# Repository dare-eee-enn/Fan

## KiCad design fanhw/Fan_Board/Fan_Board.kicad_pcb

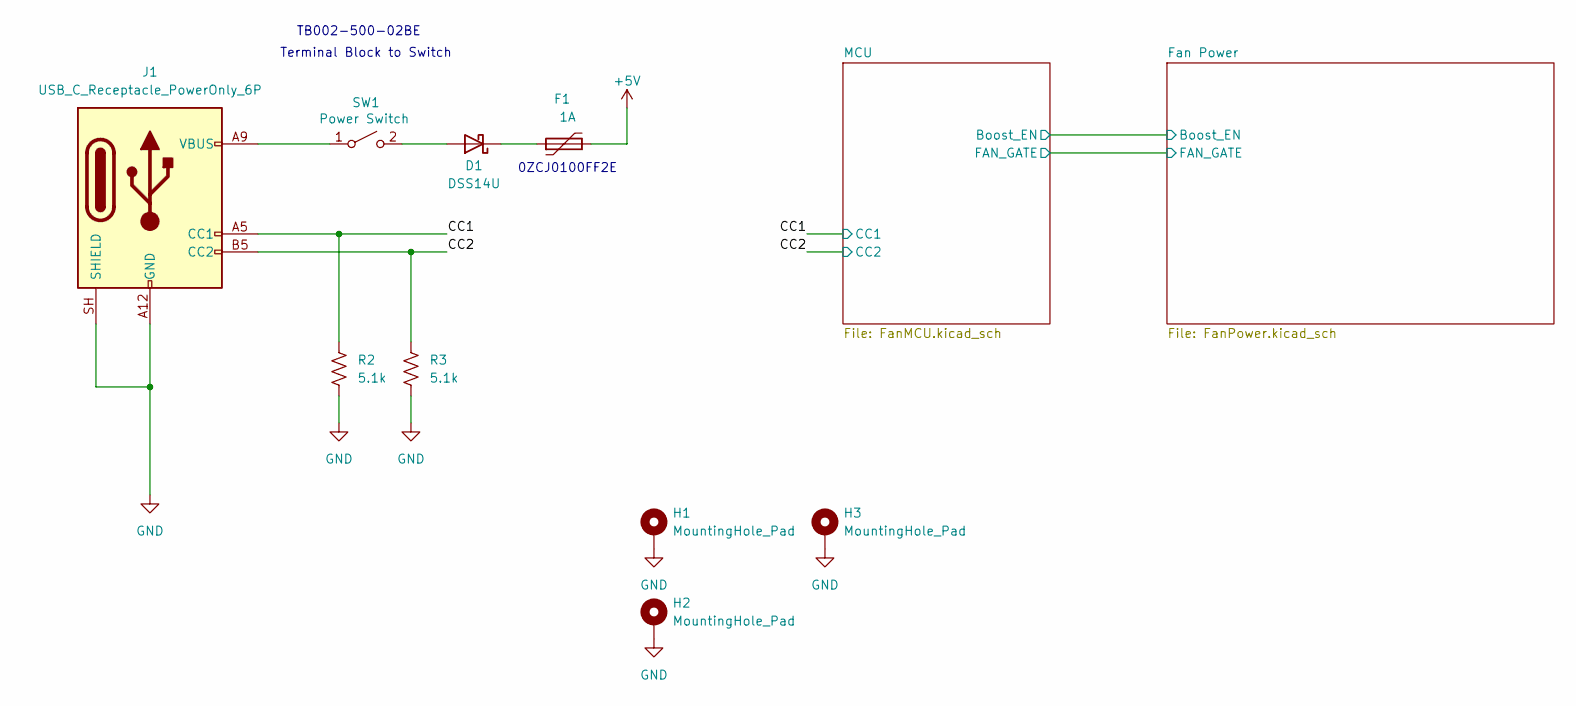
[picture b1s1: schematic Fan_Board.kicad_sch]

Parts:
D1: DSS14U; D_SOD-123F
F1: 1A; Fuse_1206_3216Metric_Pad1.42x1.75mm_HandSolder
H1, H2, H3: MountingHole_Pad; MountingHole_3.2mm_M3_DIN965_Pad
J1: USB_C_Receptacle_PowerOnly_6P; CONN_10164359-00011LF_AMP
R2, R3: 5.1k; R_0805_2012Metric_Pad1.20x1.40mm_HandSolder
SW1: Power Switch; Terminal_block

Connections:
+5V: F1.2; also elsewhere on the board
/CC1: J1.A5 (CC1), R2.1; also elsewhere on the board
/CC2: J1.B5 (CC2), R3.1; also elsewhere on the board
GND: H1.1 (1_1), H2.1 (1_1), H3.1 (1_1), J1.A12 (GND), J1.B12 (GND), J1.SH (SHIELD), R2.2, R3.2; also elsewhere on the board
unnamed: D1.2 (A), SW1.2 (B)
unnamed: D1.1 (K), F1.1
unnamed: J1.A9 (VBUS), J1.B9 (VBUS), SW1.1 (A)

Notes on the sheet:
0ZCJ0100FF2E
Terminal Block to Switch
TB002-500-02BE

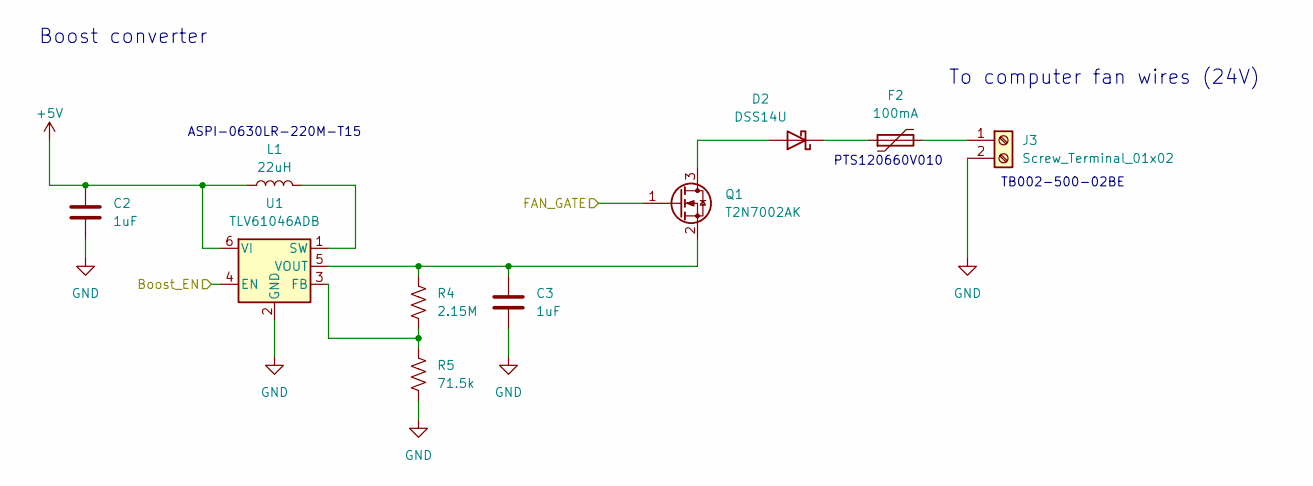
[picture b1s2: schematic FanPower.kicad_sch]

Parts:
C2, C3: 1uF; C_0805_2012Metric_Pad1.18x1.45mm_HandSolder
D2: DSS14U; D_SOD-123F
F2: 100mA; Fuse_1206_3216Metric_Pad1.42x1.75mm_HandSolder
J3: Screw_Terminal_01x02; Terminal_block
L1: 22uH; ASPI-0630LR-220M-T15
Q1: T2N7002AK; SOT-23
R4: 2.15M; R_0805_2012Metric_Pad1.20x1.40mm_HandSolder
R5: 71.5k; R_0805_2012Metric_Pad1.20x1.40mm_HandSolder
U1: TLV61046ADB; SOT-23-6

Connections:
+5V: C2.1, L1.1, U1.6 (VI); also elsewhere on the board
/Fan Power/Boost_EN: U1.4 (EN); also elsewhere on the board
/Fan Power/FAN_GATE: Q1.1 (G); also elsewhere on the board
GND: C2.2, C3.2, J3.2, R5.2, U1.2 (GND); also elsewhere on the board
unnamed: D2.2 (A), Q1.3 (D)
unnamed: D2.1 (K), F2.1
unnamed: F2.2, J3.1
unnamed: C3.1, Q1.2 (S), R4.1, U1.5 (VOUT)
unnamed: R4.2, R5.1, U1.3 (FB)
unnamed: L1.2, U1.1 (SW)

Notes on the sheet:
To computer fan wires (24V)
TB002-500-02BE
Boost converter
ASPI-0630LR-220M-T15
PTS120660V010

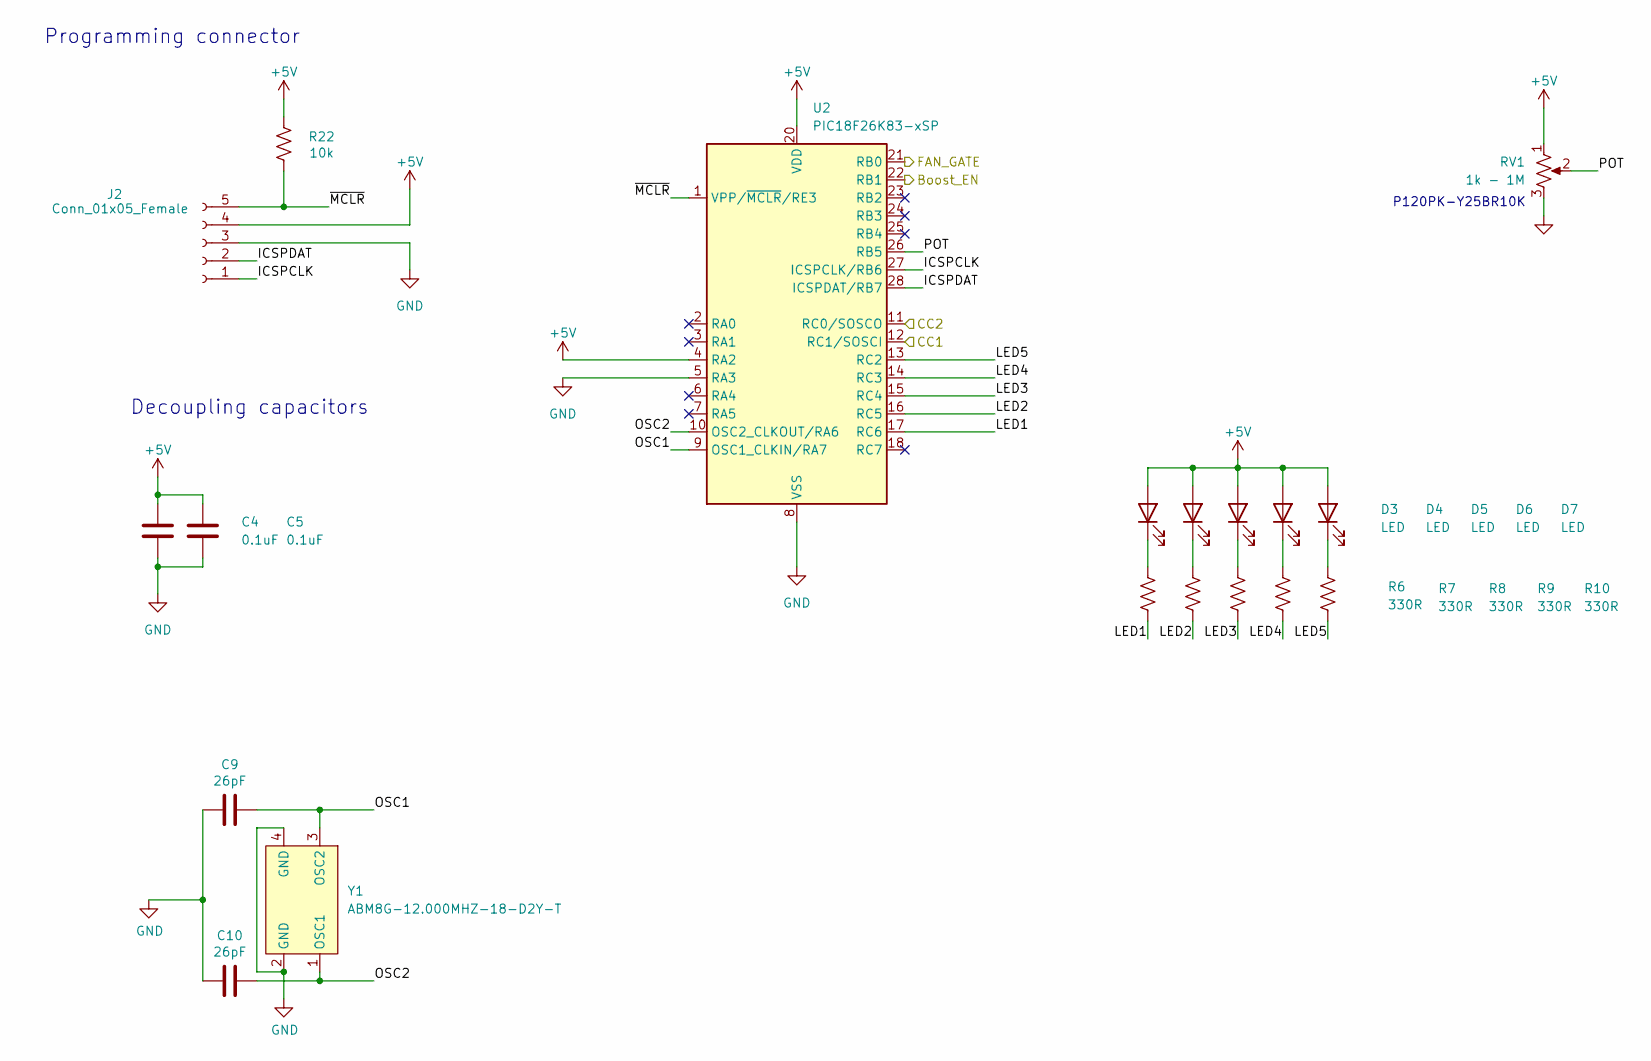
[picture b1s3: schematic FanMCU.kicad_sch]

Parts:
C4, C5: 0.1uF; C_0805_2012Metric_Pad1.18x1.45mm_HandSolder
C9, C10: 26pF; C_0805_2012Metric_Pad1.18x1.45mm_HandSolder
D3, D4, D5, D6, D7: LED; LED_1206_3216Metric_Pad1.42x1.75mm_HandSolder
J2: Conn_01x05_Female; PinSocket_5x2.54_SMD_90deg_952-3198-1-ND
R6, R7, R8, R9, R10: 330R; R_0805_2012Metric_Pad1.20x1.40mm_HandSolder
R22: 10k; R_0805_2012Metric_Pad1.20x1.40mm_HandSolder
RV1: 1k - 1M; CUI_TB007-508-03BE
U2: PIC18F26K83-xSP; SOIC-28W_7.5x18.7mm_P1.27mm
Y1: ABM8G-12.000MHZ-18-D2Y-T; Crystal_SMD_Abracon_ABM8G-4Pin_3.2x2.5mm

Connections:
+5V: C4.1, C5.1, D3.2 (A), D4.2 (A), D5.2 (A), D6.2 (A), D7.2 (A), J2.4, R22.2, RV1.1, U2.4 (RA2), U2.20 (VDD); also elsewhere on the board
/CC1: U2.12 (RC1/SOSCI); also elsewhere on the board
/CC2: U2.11 (RC0/SOSCO); also elsewhere on the board
/Fan Power/Boost_EN: U2.22 (RB1); also elsewhere on the board
/Fan Power/FAN_GATE: U2.21 (RB0); also elsewhere on the board
/MCU/ICSPCLK: J2.1, U2.27 (ICSPCLK/RB6)
/MCU/ICSPDAT: J2.2, U2.28 (ICSPDAT/RB7)
/MCU/LED1: R6.2, U2.17 (RC6)
/MCU/LED2: R7.2, U2.16 (RC5)
/MCU/LED3: R8.2, U2.15 (RC4)
/MCU/LED4: R9.2, U2.14 (RC3)
/MCU/LED5: R10.2, U2.13 (RC2)
/MCU/OSC1: C9.1, U2.9 (OSC1_CLKIN/RA7), Y1.3 (OSC2)
/MCU/OSC2: C10.1, U2.10 (OSC2_CLKOUT/RA6), Y1.1 (OSC1)
/MCU/POT: RV1.2, U2.26 (RB5)
/MCU/~MCLR: J2.5, R22.1, U2.1 (VPP/~MCLR/RE3)
GND: C4.2, C5.2, C9.2, C10.2, J2.3, RV1.3, U2.5 (RA3), U2.8 (VSS), U2.19 (VSS), Y1.2 (GND), Y1.4 (GND); also elsewhere on the board
unnamed: D3.1 (K), R6.1
unnamed: D4.1 (K), R7.1
unnamed: D5.1 (K), R8.1
unnamed: D6.1 (K), R9.1
unnamed: D7.1 (K), R10.1

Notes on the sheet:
Decoupling capacitors
Programming connector
P120PK-Y25BR10K

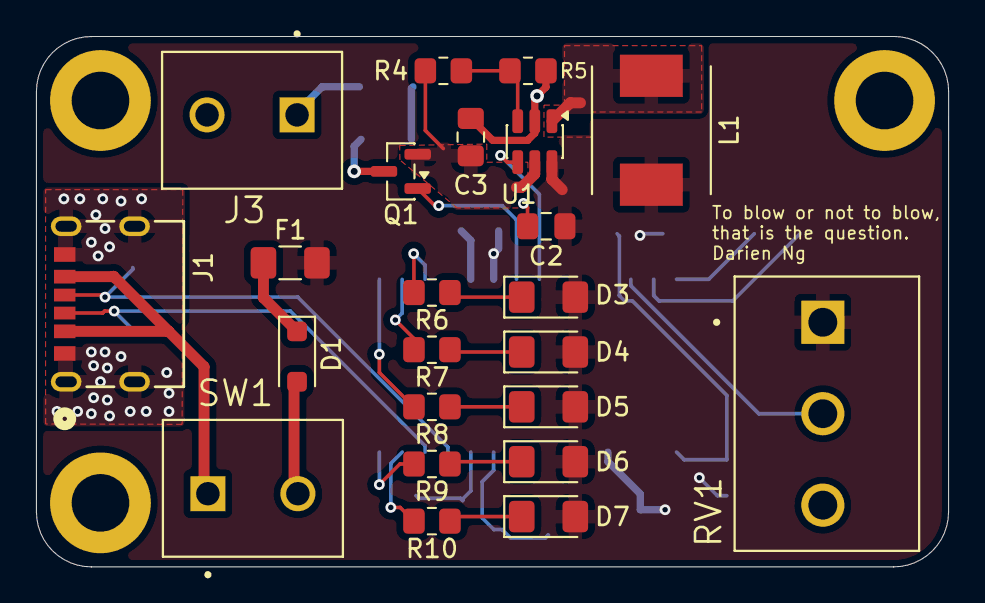
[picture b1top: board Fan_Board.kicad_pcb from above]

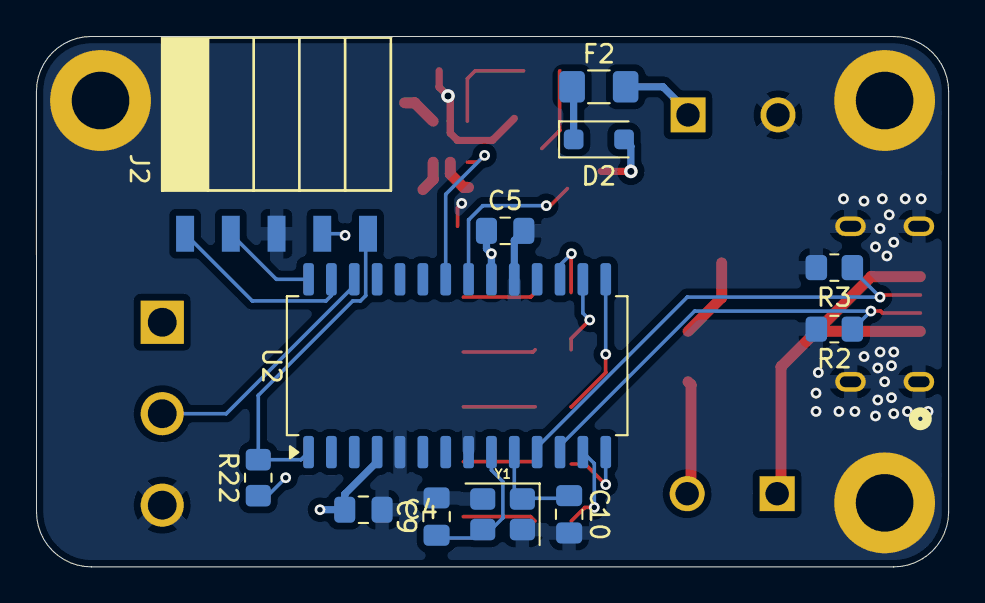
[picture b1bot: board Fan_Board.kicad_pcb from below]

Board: 2 copper layers, 50.7 x 29.5 mm, 38 parts (12 on the bottom side), 31 nets.

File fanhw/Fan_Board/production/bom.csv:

Designator,Footprint,Quantity,Value,LCSC Part #
"C10, C9",0805,2,26pF,
"C2, C3",0805,2,1uF,
"C4, C5",0805,2,0.1uF,
"D1, D2",D_SOD-123F,2,DSS14U,
"D3, D4, D5, D6, D7",1206,5,LED,
F1,1206,1,1A,
F2,1206,1,100mA,
J1,CONN_10164359-00011LF_AMP,1,USB_C_Receptacle_PowerOnly_6P,
J2,PinSocket_5x2.54_SMD_90deg_952-3198-1-ND,1,Conn_01x05_Female,
J3,Terminal_block,1,Screw_Terminal_01x02,
L1,ASPI-0630LR-220M-T15,1,22uH,
Q1,SOT-23,1,T2N7002AK,
"R10, R6, R7, R8, R9",0805,5,330R,
"R2, R3",0805,2,5.1k,
R22,0805,1,10k,
R4,0805,1,2.15M,
R5,0805,1,71.5k,
RV1,CUI_TB007-508-03BE,1,1k - 1M,
SW1,Terminal_block,1,Power Switch,
U1,SOT-23-6,1,TLV61046ADB,
U2,SOIC-28W_7.5x18.7mm_P1.27mm,1,PIC18F26K83-xSP,
Y1,Crystal_SMD_Abracon_ABM8G-4Pin_3.2x2.5mm,1,ABM8G-12.000MHZ-18-D2Y-T,

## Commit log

2026-05-04 PCB first draft
2026-05-09 Small edits, production files
2026-05-11 added oscillator, regen prod files
